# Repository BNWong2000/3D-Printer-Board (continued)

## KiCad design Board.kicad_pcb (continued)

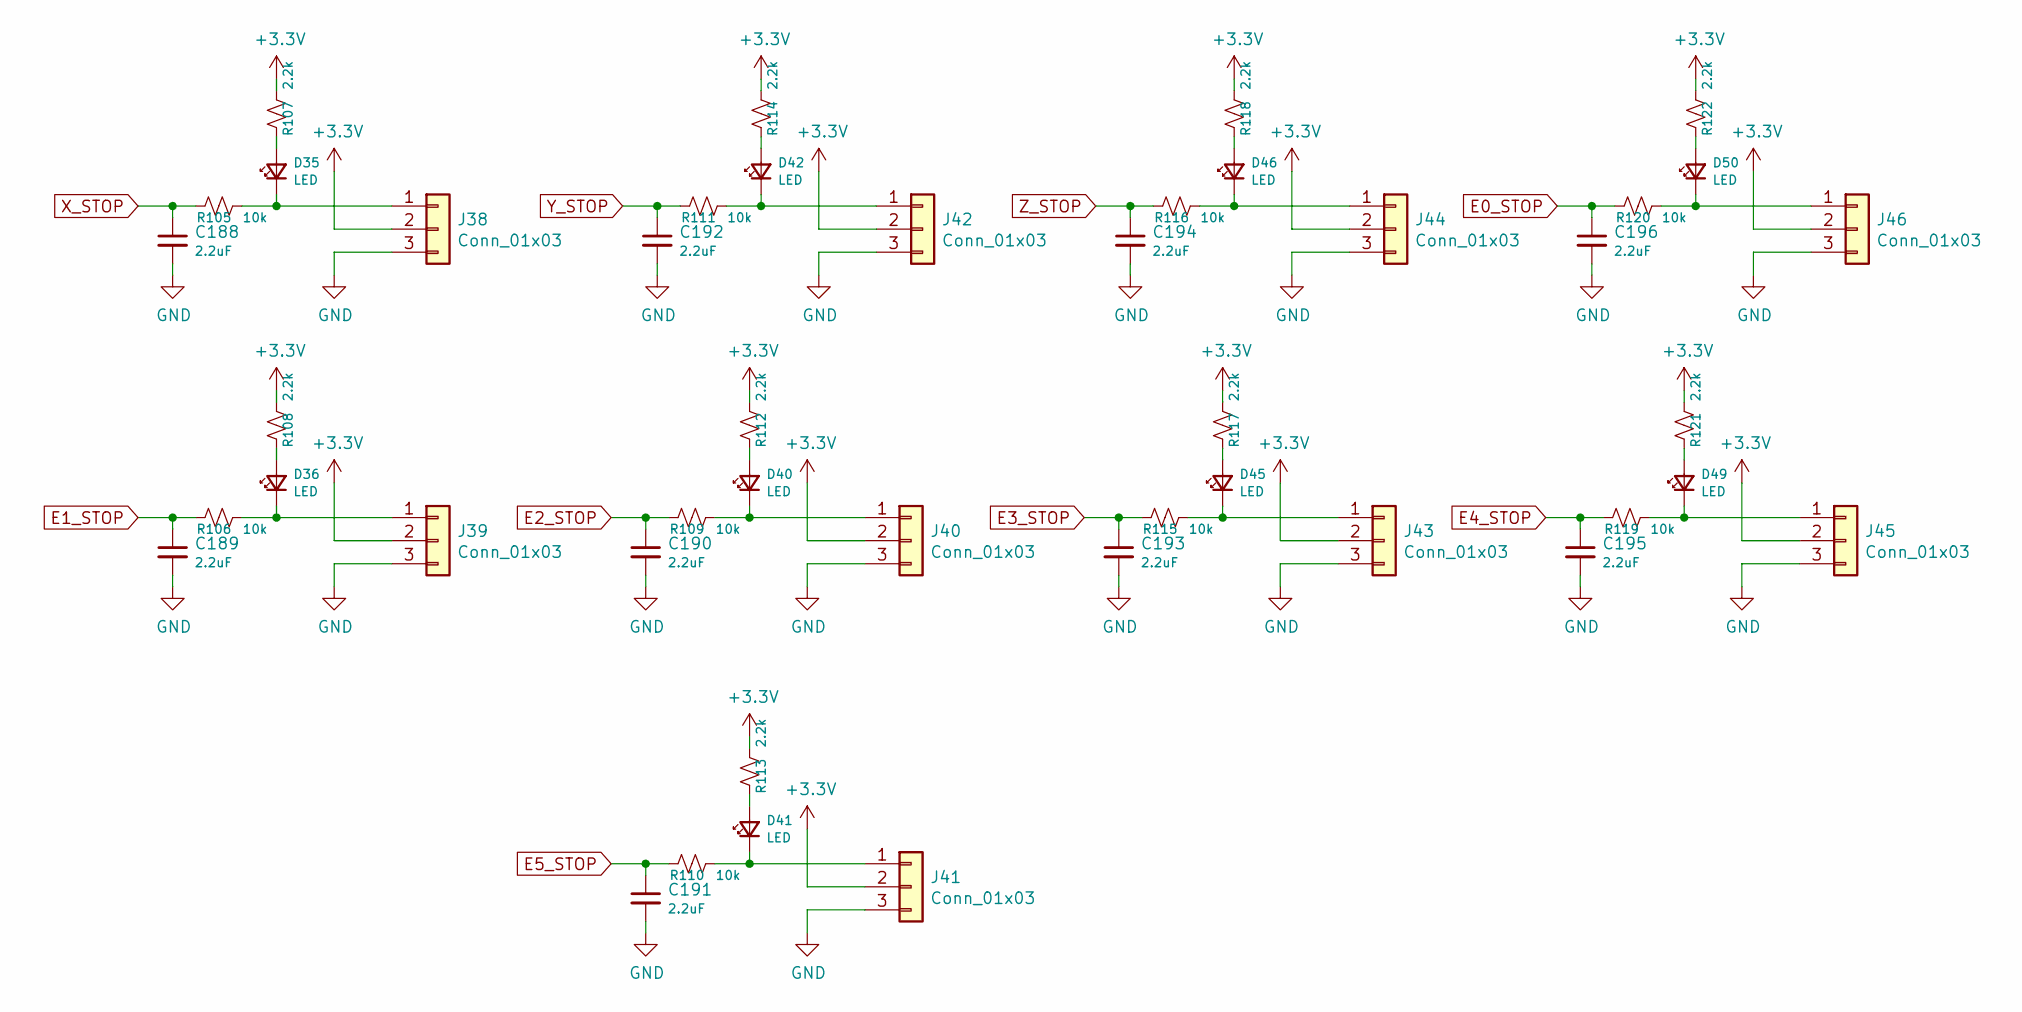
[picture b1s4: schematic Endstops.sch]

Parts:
C188, C189, C190, C191, C192, C193, C194, C195, C196: 2.2uF; C_0603_1608Metric_Pad1.05x0.95mm_HandSolder
D35, D36, D40, D41, D42, D45, D46, D49, D50: LED; LED_0603_1608Metric_Pad1.05x0.95mm_HandSolder
J38, J39, J40, J41, J42, J43, J44, J45, J46: Conn_01x03; Molex_KK-254_AE-6410-03A_1x03_P2.54mm_Vertical
R105, R106, R109, R110, R111, R115, R116, R119, R120: 10k; R_0603_1608Metric_Pad1.05x0.95mm_HandSolder
R107, R108, R112, R113, R114, R117, R118, R121, R122: 2.2k; R_0603_1608Metric_Pad1.05x0.95mm_HandSolder

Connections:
+3V3: J38.2, J39.2, J40.2, J41.2, J42.2, J43.2, J44.2, J45.2, J46.2, R107.1, R108.1, R112.1, R113.1, R114.1, R117.1, R118.1, R121.1, R122.1; also elsewhere on the board
E0_STOP: C196.1, R120.2; also elsewhere on the board
E1_STOP: C189.1, R106.2; also elsewhere on the board
E2_STOP: C190.1, R109.2; also elsewhere on the board
E3_STOP: C193.1, R115.2; also elsewhere on the board
E4_STOP: C195.1, R119.2; also elsewhere on the board
E5_STOP: C191.1, R110.2; also elsewhere on the board
GND: C188.2, C189.2, C190.2, C191.2, C192.2, C193.2, C194.2, C195.2, C196.2, J38.3, J39.3, J40.3, J41.3, J42.3, J43.3, J44.3, J45.3, J46.3; also elsewhere on the board
unnamed: D35.1 (K), J38.1, R105.1
unnamed: D35.2 (A), R107.2
unnamed: D36.1 (K), J39.1, R106.1
unnamed: D36.2 (A), R108.2
unnamed: D40.1 (K), J40.1, R109.1
unnamed: D40.2 (A), R112.2
unnamed: D41.1 (K), J41.1, R110.1
unnamed: D41.2 (A), R113.2
unnamed: D42.1 (K), J42.1, R111.1
unnamed: D42.2 (A), R114.2
unnamed: D45.1 (K), J43.1, R115.1
unnamed: D45.2 (A), R117.2
unnamed: D46.1 (K), J44.1, R116.1
unnamed: D46.2 (A), R118.2
unnamed: D49.1 (K), J45.1, R119.1
unnamed: D49.2 (A), R121.2
unnamed: D50.1 (K), J46.1, R120.1
unnamed: D50.2 (A), R122.2
X_STOP: C188.1, R105.2; also elsewhere on the board
Y_STOP: C192.1, R111.2; also elsewhere on the board
Z_STOP: C194.1, R116.2; also elsewhere on the board

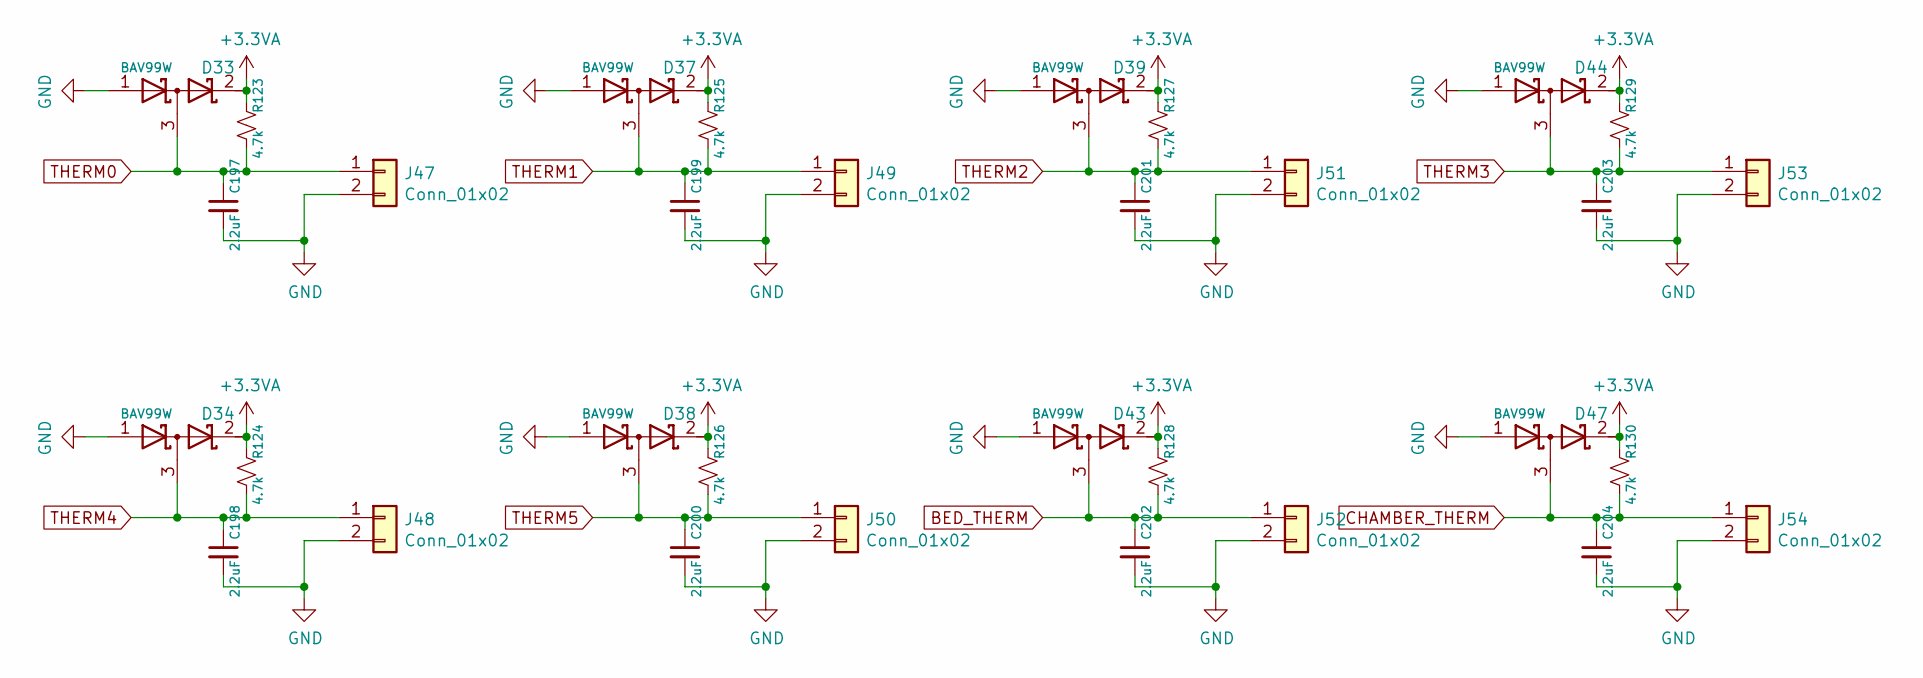
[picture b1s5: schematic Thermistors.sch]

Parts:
C197, C198, C199, C200, C201, C202, C203, C204: 2.2uF; C_0603_1608Metric_Pad1.05x0.95mm_HandSolder
D33, D34, D37, D38, D39, D43, D44, D47: BAV99W; SOT-323_SC-70_Handsoldering
J47, J48, J49, J50, J51, J52, J53, J54: Conn_01x02; Molex_KK-254_AE-6410-02A_1x02_P2.54mm_Vertical
R123, R124, R125, R126, R127, R128, R129, R130: 4.7k; R_0603_1608Metric_Pad1.05x0.95mm_HandSolder

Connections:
+3.3VA: D33.2 (K), D34.2 (K), D37.2 (K), D38.2 (K), D39.2 (K), D43.2 (K), D44.2 (K), D47.2 (K), R123.1, R124.1, R125.1, R126.1, R127.1, R128.1, R129.1, R130.1; also elsewhere on the board
BED_THERM: C202.1, D43.3 (common), J52.1, R128.2; also elsewhere on the board
CHAMBER_THERM: C204.1, D47.3 (common), J54.1, R130.2; also elsewhere on the board
GND: C197.2, C198.2, C199.2, C200.2, C201.2, C202.2, C203.2, C204.2, D33.1 (A), D34.1 (A), D37.1 (A), D38.1 (A), D39.1 (A), D43.1 (A), D44.1 (A), D47.1 (A), J47.2, J48.2, J49.2, J50.2, J51.2, J52.2, J53.2, J54.2; also elsewhere on the board
THERM0: C197.1, D33.3 (common), J47.1, R123.2; also elsewhere on the board
THERM1: C199.1, D37.3 (common), J49.1, R125.2; also elsewhere on the board
THERM2: C201.1, D39.3 (common), J51.1, R127.2; also elsewhere on the board
THERM3: C203.1, D44.3 (common), J53.1, R129.2; also elsewhere on the board
THERM4: C198.1, D34.3 (common), J48.1, R124.2; also elsewhere on the board
THERM5: C200.1, D38.3 (common), J50.1, R126.2; also elsewhere on the board

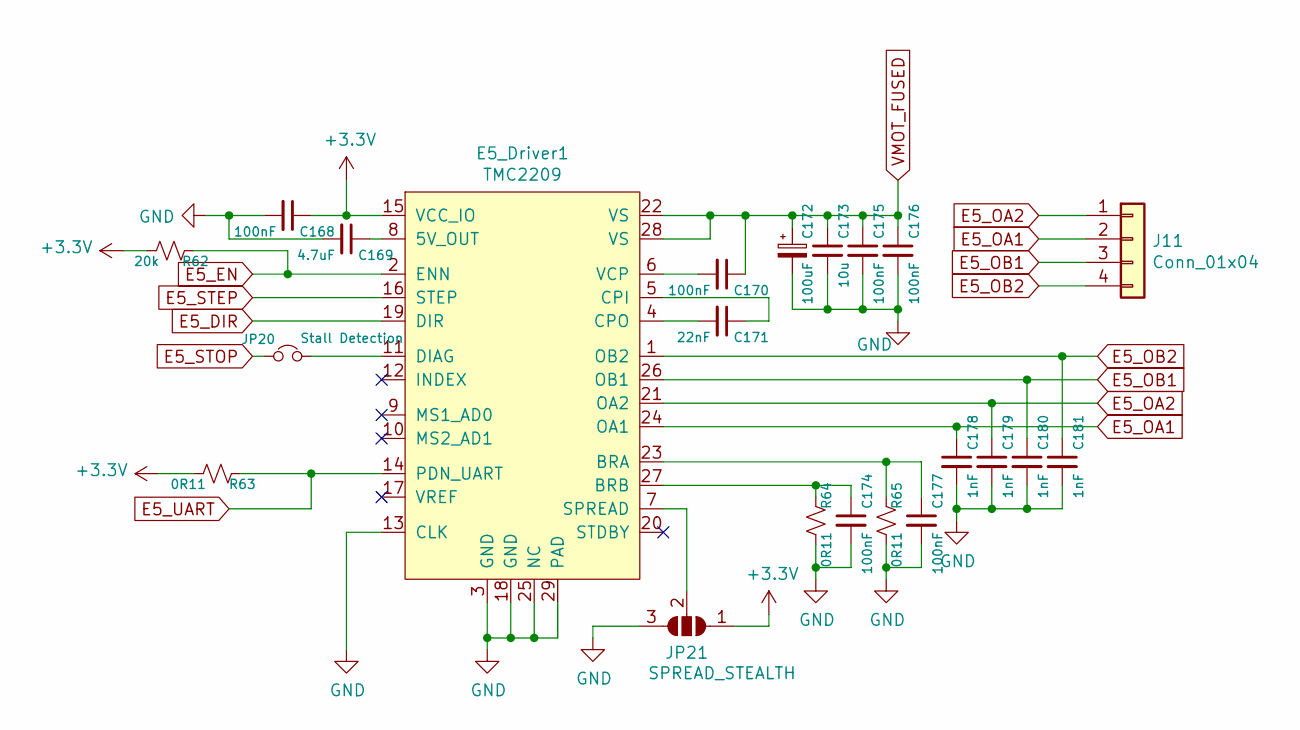
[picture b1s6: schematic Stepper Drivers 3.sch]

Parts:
C168, C170, C174, C175, C176, C177: 100nF; C_0603_1608Metric_Pad1.05x0.95mm_HandSolder
C169: 4.7uF; C_0805_2012Metric_Pad1.15x1.40mm_HandSolder
C171: 22nF; C_0603_1608Metric_Pad1.05x0.95mm_HandSolder
C172: 100uF; CP_Elec_6.3x7.7
C173: 10u; C_0805_2012Metric_Pad1.15x1.40mm_HandSolder
C178, C179, C180, C181: 1nF; C_0603_1608Metric_Pad1.05x0.95mm_HandSolder
E5_Driver1: TMC2209
J11: Conn_01x04; Molex_KK-254_AE-6410-04A_1x04_P2.54mm_Vertical
JP20: Stall Detection; PinHeader_1x02_P2.54mm_Vertical
JP21: SPREAD_STEALTH; PinHeader_1x03_P2.54mm_Vertical
R62: 20k
R63, R64, R65: 0R11

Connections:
+3V3: C168.1, E5_Driver1.15 (VCC_IO), JP21.1 (A), R62.2, R63.2; also elsewhere on the board
E5_DIR: E5_Driver1.19 (DIR); also elsewhere on the board
E5_EN: E5_Driver1.2 (ENN), R62.1; also elsewhere on the board
E5_OA1: C178.1, E5_Driver1.24 (OA1), J11.2
E5_OA2: C179.1, E5_Driver1.21 (OA2), J11.1
E5_OB1: C180.1, E5_Driver1.26 (OB1), J11.3
E5_OB2: C181.1, E5_Driver1.1 (OB2), J11.4
E5_STEP: E5_Driver1.16 (STEP); also elsewhere on the board
E5_STOP: JP20.1; also elsewhere on the board
E5_UART: E5_Driver1.14 (PDN_UART), R63.1; also elsewhere on the board
GND: C168.2, C169.2, C172.2, C173.2, C174.2, C175.2, C176.2, C177.2, C178.2, C179.2, C180.2, C181.2, E5_Driver1.3 (GND), E5_Driver1.13 (CLK), E5_Driver1.18 (GND), E5_Driver1.25 (NC), E5_Driver1.29 (PAD), JP21.3 (B), R64.2, R65.2; also elsewhere on the board
unnamed: C169.1, E5_Driver1.8 (5V_OUT)
unnamed: C170.2, E5_Driver1.6 (VCP)
unnamed: C171.1, E5_Driver1.5 (CPI)
unnamed: C171.2, E5_Driver1.4 (CPO)
unnamed: C174.1, E5_Driver1.27 (BRB), R64.1
unnamed: C177.1, E5_Driver1.23 (BRA), R65.1
unnamed: E5_Driver1.7 (SPREAD), JP21.2 (C)
unnamed: E5_Driver1.11 (DIAG), JP20.2
VMOT_FUSED: C170.1, C172.1, C173.1, C175.1, C176.1, E5_Driver1.22 (VS), E5_Driver1.28 (VS); also elsewhere on the board

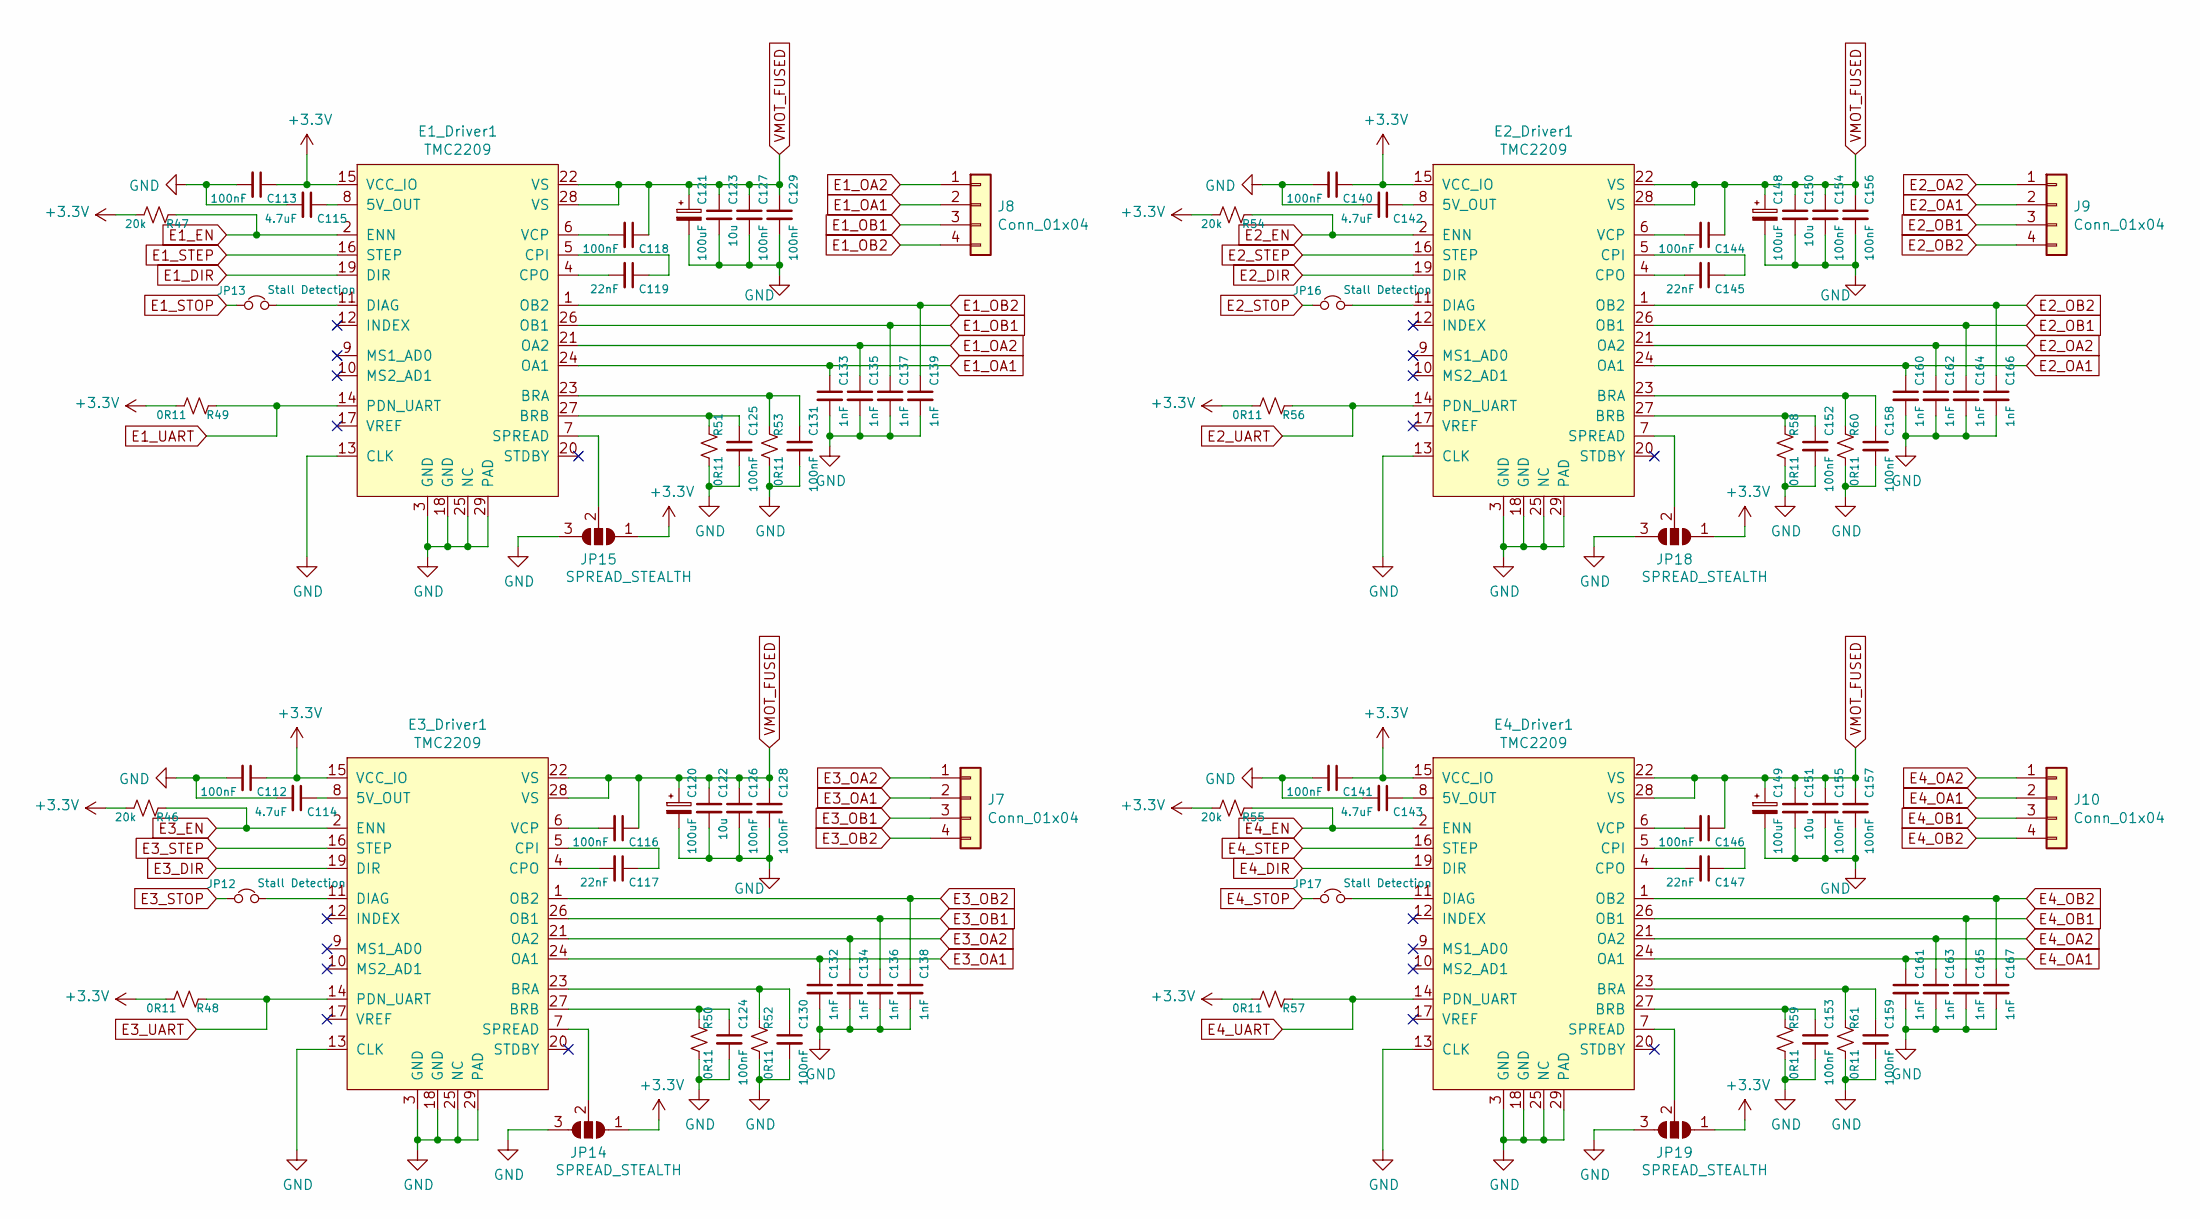
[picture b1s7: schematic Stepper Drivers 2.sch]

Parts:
C112, C113, C116, C118, C124, C125, C126, C127, C128, C129, C130, C131, C140, C141, C144, C146, C152, C153, C154, C155, C156, C157, C158, C159: 100nF; C_0603_1608Metric_Pad1.05x0.95mm_HandSolder
C114, C115, C142, C143: 4.7uF; C_0805_2012Metric_Pad1.15x1.40mm_HandSolder
C117, C119, C145, C147: 22nF; C_0603_1608Metric_Pad1.05x0.95mm_HandSolder
C120, C121, C148, C149: 100uF; CP_Elec_6.3x7.7
C122, C123, C150, C151: 10u; C_0805_2012Metric_Pad1.15x1.40mm_HandSolder
C132, C133, C134, C135, C136, C137, C138, C139, C160, C161, C162, C163, C164, C165, C166, C167: 1nF; C_0603_1608Metric_Pad1.05x0.95mm_HandSolder
E1_Driver1, E2_Driver1, E3_Driver1, E4_Driver1: TMC2209; QFN-28-1EP_5x5mm_P0.5mm_EP3.35x3.35mm_ThermalVias
J7, J8, J9, J10: Conn_01x04; Molex_KK-254_AE-6410-04A_1x04_P2.54mm_Vertical
JP12, JP13, JP16, JP17: Stall Detection; PinHeader_1x02_P2.54mm_Vertical
JP14, JP15, JP18, JP19: SPREAD_STEALTH; SolderJumper-3_P1.3mm_Open_RoundedPad1.0x1.5mm
R46, R47, R54, R55: 20k; R_0603_1608Metric_Pad1.05x0.95mm_HandSolder
R48, R49, R50, R51, R52, R53, R56, R57, R58, R59, R60, R61: 0R11; R_0805_2012Metric_Pad1.15x1.40mm_HandSolder

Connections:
+3V3: C112.1, C113.1, C140.1, C141.1, E1_Driver1.15 (VCC_IO), E2_Driver1.15 (VCC_IO), E3_Driver1.15 (VCC_IO), E4_Driver1.15 (VCC_IO), JP14.1 (A), JP15.1 (A), JP18.1 (A), JP19.1 (A), R46.2, R47.2, R48.2, R49.2, R54.2, R55.2, R56.2, R57.2; also elsewhere on the board
E1_DIR: E1_Driver1.19 (DIR); also elsewhere on the board
E1_EN: E1_Driver1.2 (ENN), R47.1; also elsewhere on the board
E1_OA1: C133.1, E1_Driver1.24 (OA1), J8.2
E1_OA2: C135.1, E1_Driver1.21 (OA2), J8.1
E1_OB1: C137.1, E1_Driver1.26 (OB1), J8.3
E1_OB2: C139.1, E1_Driver1.1 (OB2), J8.4
E1_STEP: E1_Driver1.16 (STEP); also elsewhere on the board
E1_STOP: JP13.1; also elsewhere on the board
E1_UART: E1_Driver1.14 (PDN_UART), R49.1; also elsewhere on the board
E2_DIR: E2_Driver1.19 (DIR); also elsewhere on the board
E2_EN: E2_Driver1.2 (ENN), R54.1; also elsewhere on the board
E2_OA1: C160.1, E2_Driver1.24 (OA1), J9.2
E2_OA2: C162.1, E2_Driver1.21 (OA2), J9.1
E2_OB1: C164.1, E2_Driver1.26 (OB1), J9.3
E2_OB2: C166.1, E2_Driver1.1 (OB2), J9.4
E2_STEP: E2_Driver1.16 (STEP); also elsewhere on the board
E2_STOP: JP16.1; also elsewhere on the board
E2_UART: E2_Driver1.14 (PDN_UART), R56.1; also elsewhere on the board
E3_DIR: E3_Driver1.19 (DIR); also elsewhere on the board
E3_EN: E3_Driver1.2 (ENN), R46.1; also elsewhere on the board
E3_OA1: C132.1, E3_Driver1.24 (OA1), J7.2
E3_OA2: C134.1, E3_Driver1.21 (OA2), J7.1
E3_OB1: C136.1, E3_Driver1.26 (OB1), J7.3
E3_OB2: C138.1, E3_Driver1.1 (OB2), J7.4
E3_STEP: E3_Driver1.16 (STEP); also elsewhere on the board
E3_STOP: JP12.1; also elsewhere on the board
E3_UART: E3_Driver1.14 (PDN_UART), R48.1; also elsewhere on the board
E4_DIR: E4_Driver1.19 (DIR); also elsewhere on the board
E4_EN: E4_Driver1.2 (ENN), R55.1; also elsewhere on the board
E4_OA1: C161.1, E4_Driver1.24 (OA1), J10.2
E4_OA2: C163.1, E4_Driver1.21 (OA2), J10.1
E4_OB1: C165.1, E4_Driver1.26 (OB1), J10.3
E4_OB2: C167.1, E4_Driver1.1 (OB2), J10.4
E4_STEP: E4_Driver1.16 (STEP); also elsewhere on the board
E4_STOP: JP17.1; also elsewhere on the board
E4_UART: E4_Driver1.14 (PDN_UART), R57.1; also elsewhere on the board
GND: C112.2, C113.2, C114.2, C115.2, C120.2, C121.2, C122.2, C123.2, C124.2, C125.2, C126.2, C127.2, C128.2, C129.2, C130.2, C131.2, C132.2, C133.2, C134.2, C135.2, C136.2, C137.2, C138.2, C139.2, C140.2, C141.2, C142.2, C143.2, C148.2, C149.2, C150.2, C151.2, C152.2, C153.2, C154.2, C155.2, C156.2, C157.2, C158.2, C159.2, C160.2, C161.2, C162.2, C163.2, C164.2, C165.2, C166.2, C167.2, E1_Driver1.3 (GND), E1_Driver1.13 (CLK), E1_Driver1.18 (GND), E1_Driver1.25 (NC), E1_Driver1.29 (PAD), E2_Driver1.3 (GND), E2_Driver1.13 (CLK), E2_Driver1.18 (GND), E2_Driver1.25 (NC), E2_Driver1.29 (PAD), E3_Driver1.3 (GND), E3_Driver1.13 (CLK), E3_Driver1.18 (GND), E3_Driver1.25 (NC), E3_Driver1.29 (PAD), E4_Driver1.3 (GND), E4_Driver1.13 (CLK), E4_Driver1.18 (GND), E4_Driver1.25 (NC), E4_Driver1.29 (PAD), JP14.3 (B), JP15.3 (B), JP18.3 (B), JP19.3 (B), R50.2, R51.2, R52.2, R53.2, R58.2, R59.2, R60.2, R61.2; also elsewhere on the board
unnamed: C114.1, E3_Driver1.8 (5V_OUT)
unnamed: C115.1, E1_Driver1.8 (5V_OUT)
unnamed: C116.2, E3_Driver1.6 (VCP)
unnamed: C117.1, E3_Driver1.5 (CPI)
unnamed: C117.2, E3_Driver1.4 (CPO)
unnamed: C118.2, E1_Driver1.6 (VCP)
unnamed: C119.1, E1_Driver1.5 (CPI)
unnamed: C119.2, E1_Driver1.4 (CPO)
unnamed: C124.1, E3_Driver1.27 (BRB), R50.1
unnamed: C125.1, E1_Driver1.27 (BRB), R51.1
unnamed: C130.1, E3_Driver1.23 (BRA), R52.1
unnamed: C131.1, E1_Driver1.23 (BRA), R53.1
unnamed: C142.1, E2_Driver1.8 (5V_OUT)
unnamed: C143.1, E4_Driver1.8 (5V_OUT)
unnamed: C144.2, E2_Driver1.6 (VCP)
unnamed: C145.1, E2_Driver1.5 (CPI)
unnamed: C145.2, E2_Driver1.4 (CPO)
unnamed: C146.2, E4_Driver1.6 (VCP)
unnamed: C147.1, E4_Driver1.5 (CPI)
unnamed: C147.2, E4_Driver1.4 (CPO)
unnamed: C152.1, E2_Driver1.27 (BRB), R58.1
unnamed: C153.1, E4_Driver1.27 (BRB), R59.1
unnamed: C158.1, E2_Driver1.23 (BRA), R60.1
unnamed: C159.1, E4_Driver1.23 (BRA), R61.1
unnamed: E1_Driver1.7 (SPREAD), JP15.2 (C)
unnamed: E1_Driver1.11 (DIAG), JP13.2
unnamed: E2_Driver1.7 (SPREAD), JP18.2 (C)
unnamed: E2_Driver1.11 (DIAG), JP16.2
unnamed: E3_Driver1.7 (SPREAD), JP14.2 (C)
unnamed: E3_Driver1.11 (DIAG), JP12.2
unnamed: E4_Driver1.7 (SPREAD), JP19.2 (C)
unnamed: E4_Driver1.11 (DIAG), JP17.2
VMOT_FUSED: C116.1, C118.1, C120.1, C121.1, C122.1, C123.1, C126.1, C127.1, C128.1, C129.1, C144.1, C146.1, C148.1, C149.1, C150.1, C151.1, C154.1, C155.1, C156.1, C157.1, E1_Driver1.22 (VS), E1_Driver1.28 (VS), E2_Driver1.22 (VS), E2_Driver1.28 (VS), E3_Driver1.22 (VS), E3_Driver1.28 (VS), E4_Driver1.22 (VS), E4_Driver1.28 (VS); also elsewhere on the board

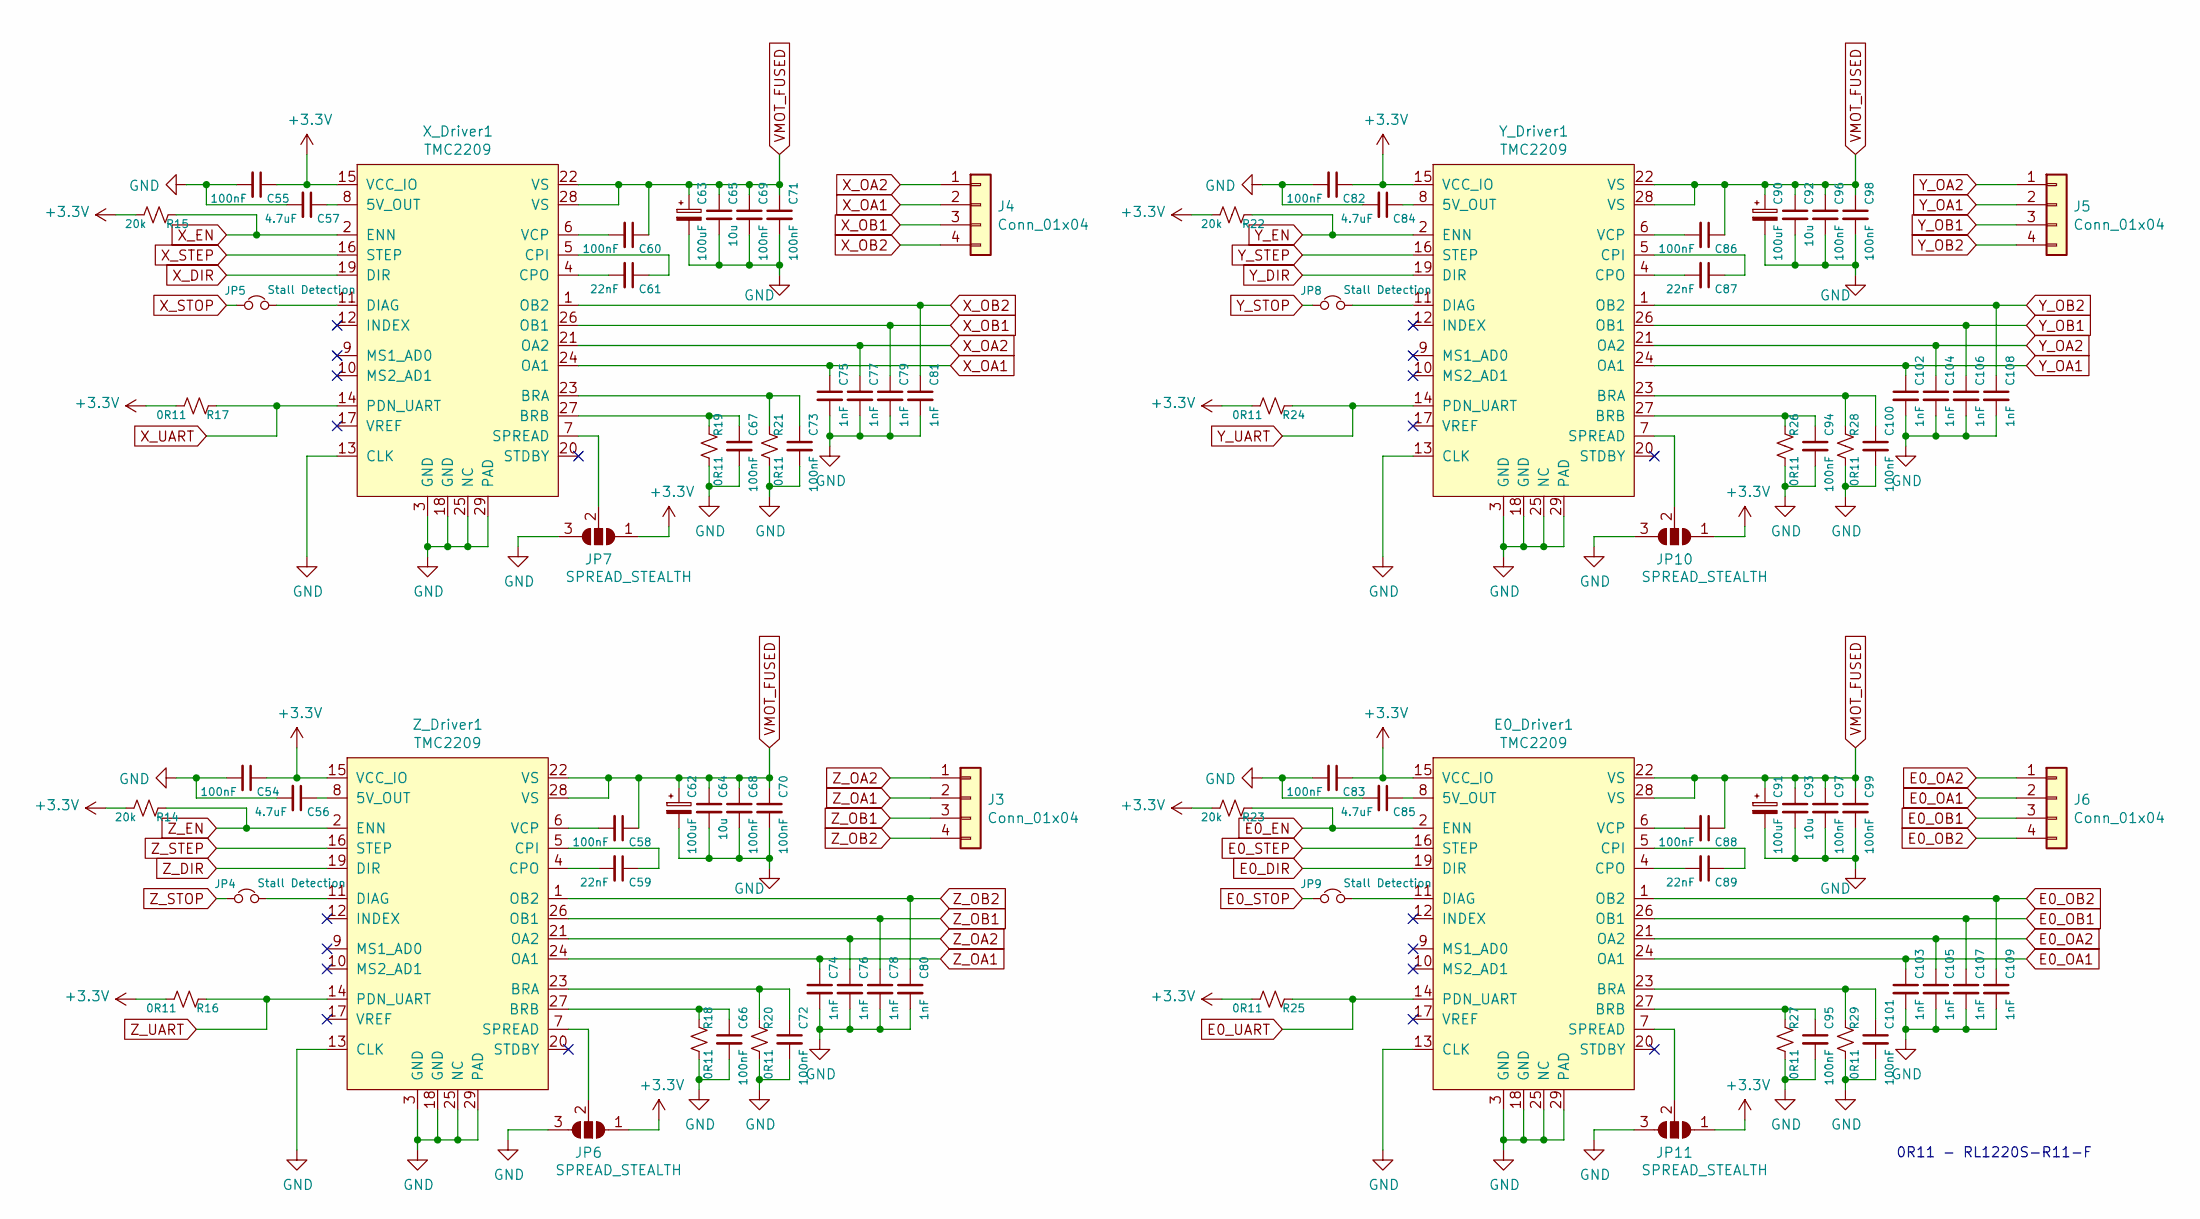
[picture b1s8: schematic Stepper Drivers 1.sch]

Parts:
C54, C55, C58, C60, C66, C67, C68, C69, C70, C71, C72, C73, C82, C83, C86, C88, C94, C95, C96, C97, C98, C99, C100, C101: 100nF; C_0603_1608Metric_Pad1.05x0.95mm_HandSolder
C56, C57, C84, C85: 4.7uF; C_0805_2012Metric_Pad1.15x1.40mm_HandSolder
C59, C61, C87, C89: 22nF; C_0603_1608Metric_Pad1.05x0.95mm_HandSolder
C62, C63, C90, C91: 100uF; CP_Elec_6.3x7.7
C64, C65, C92, C93: 10u; C_0805_2012Metric_Pad1.15x1.40mm_HandSolder
C74, C75, C76, C77, C78, C79, C80, C81, C102, C103, C104, C105, C106, C107, C108, C109: 1nF; C_0603_1608Metric_Pad1.05x0.95mm_HandSolder
E0_Driver1: TMC2209; QFN-28-1EP_5x5mm_P0.5mm_EP3.35x3.35mm_ThermalVias
J3, J4, J5, J6: Conn_01x04; Molex_KK-254_AE-6410-04A_1x04_P2.54mm_Vertical
JP4, JP5, JP8, JP9: Stall Detection; PinHeader_1x02_P2.54mm_Vertical
JP6, JP7, JP10, JP11: SPREAD_STEALTH; SolderJumper-3_P1.3mm_Open_RoundedPad1.0x1.5mm
R14, R15, R22, R23: 20k; R_0603_1608Metric_Pad1.05x0.95mm_HandSolder
R16, R17, R18, R19, R20, R21, R24, R25, R26, R27, R28, R29: 0R11; R_0805_2012Metric_Pad1.15x1.40mm_HandSolder
X_Driver1: TMC2209; QFN-28-1EP_5x5mm_P0.5mm_EP3.35x3.35mm_ThermalVias
Y_Driver1: TMC2209; QFN-28-1EP_5x5mm_P0.5mm_EP3.35x3.35mm_ThermalVias
Z_Driver1: TMC2209; QFN-28-1EP_5x5mm_P0.5mm_EP3.35x3.35mm_ThermalVias

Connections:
+3V3: C54.1, C55.1, C82.1, C83.1, E0_Driver1.15 (VCC_IO), JP6.1 (A), JP7.1 (A), JP10.1 (A), JP11.1 (A), R14.2, R15.2, R16.2, R17.2, R22.2, R23.2, R24.2, R25.2, X_Driver1.15 (VCC_IO), Y_Driver1.15 (VCC_IO), Z_Driver1.15 (VCC_IO); also elsewhere on the board
E0_DIR: E0_Driver1.19 (DIR); also elsewhere on the board
E0_EN: E0_Driver1.2 (ENN), R23.1; also elsewhere on the board
E0_OA1: C103.1, E0_Driver1.24 (OA1), J6.2
E0_OA2: C105.1, E0_Driver1.21 (OA2), J6.1
E0_OB1: C107.1, E0_Driver1.26 (OB1), J6.3
E0_OB2: C109.1, E0_Driver1.1 (OB2), J6.4
E0_STEP: E0_Driver1.16 (STEP); also elsewhere on the board
E0_STOP: JP9.1; also elsewhere on the board
E0_UART: E0_Driver1.14 (PDN_UART), R25.1; also elsewhere on the board
GND: C54.2, C55.2, C56.2, C57.2, C62.2, C63.2, C64.2, C65.2, C66.2, C67.2, C68.2, C69.2, C70.2, C71.2, C72.2, C73.2, C74.2, C75.2, C76.2, C77.2, C78.2, C79.2, C80.2, C81.2, C82.2, C83.2, C84.2, C85.2, C90.2, C91.2, C92.2, C93.2, C94.2, C95.2, C96.2, C97.2, C98.2, C99.2, C100.2, C101.2, C102.2, C103.2, C104.2, C105.2, C106.2, C107.2, C108.2, C109.2, E0_Driver1.3 (GND), E0_Driver1.13 (CLK), E0_Driver1.18 (GND), E0_Driver1.25 (NC), E0_Driver1.29 (PAD), JP6.3 (B), JP7.3 (B), JP10.3 (B), JP11.3 (B), R18.2, R19.2, R20.2, R21.2, R26.2, R27.2, R28.2, R29.2, X_Driver1.3 (GND), X_Driver1.13 (CLK), X_Driver1.18 (GND), X_Driver1.25 (NC), X_Driver1.29 (PAD), Y_Driver1.3 (GND), Y_Driver1.13 (CLK), Y_Driver1.18 (GND), Y_Driver1.25 (NC), Y_Driver1.29 (PAD), Z_Driver1.3 (GND), Z_Driver1.13 (CLK), Z_Driver1.18 (GND), Z_Driver1.25 (NC), Z_Driver1.29 (PAD); also elsewhere on the board
unnamed: C56.1, Z_Driver1.8 (5V_OUT)
unnamed: C57.1, X_Driver1.8 (5V_OUT)
unnamed: C58.2, Z_Driver1.6 (VCP)
unnamed: C59.1, Z_Driver1.5 (CPI)
unnamed: C59.2, Z_Driver1.4 (CPO)
unnamed: C60.2, X_Driver1.6 (VCP)
unnamed: C61.1, X_Driver1.5 (CPI)
unnamed: C61.2, X_Driver1.4 (CPO)
unnamed: C66.1, R18.1, Z_Driver1.27 (BRB)
unnamed: C67.1, R19.1, X_Driver1.27 (BRB)
unnamed: C72.1, R20.1, Z_Driver1.23 (BRA)
unnamed: C73.1, R21.1, X_Driver1.23 (BRA)
unnamed: C84.1, Y_Driver1.8 (5V_OUT)
unnamed: C85.1, E0_Driver1.8 (5V_OUT)
unnamed: C86.2, Y_Driver1.6 (VCP)
unnamed: C87.1, Y_Driver1.5 (CPI)
unnamed: C87.2, Y_Driver1.4 (CPO)
unnamed: C88.2, E0_Driver1.6 (VCP)
unnamed: C89.1, E0_Driver1.5 (CPI)
unnamed: C89.2, E0_Driver1.4 (CPO)
unnamed: C94.1, R26.1, Y_Driver1.27 (BRB)
unnamed: C95.1, E0_Driver1.27 (BRB), R27.1
unnamed: C100.1, R28.1, Y_Driver1.23 (BRA)
unnamed: C101.1, E0_Driver1.23 (BRA), R29.1
unnamed: E0_Driver1.7 (SPREAD), JP11.2 (C)
unnamed: E0_Driver1.11 (DIAG), JP9.2
unnamed: JP4.2, Z_Driver1.11 (DIAG)
unnamed: JP5.2, X_Driver1.11 (DIAG)
unnamed: JP6.2 (C), Z_Driver1.7 (SPREAD)
unnamed: JP7.2 (C), X_Driver1.7 (SPREAD)
unnamed: JP8.2, Y_Driver1.11 (DIAG)
unnamed: JP10.2 (C), Y_Driver1.7 (SPREAD)
VMOT_FUSED: C58.1, C60.1, C62.1, C63.1, C64.1, C65.1, C68.1, C69.1, C70.1, C71.1, C86.1, C88.1, C90.1, C91.1, C92.1, C93.1, C96.1, C97.1, C98.1, C99.1, E0_Driver1.22 (VS), E0_Driver1.28 (VS), X_Driver1.22 (VS), X_Driver1.28 (VS), Y_Driver1.22 (VS), Y_Driver1.28 (VS), Z_Driver1.22 (VS), Z_Driver1.28 (VS); also elsewhere on the board
X_DIR: X_Driver1.19 (DIR); also elsewhere on the board
X_EN: R15.1, X_Driver1.2 (ENN); also elsewhere on the board
X_OA1: C75.1, J4.2, X_Driver1.24 (OA1)
X_OA2: C77.1, J4.1, X_Driver1.21 (OA2)
X_OB1: C79.1, J4.3, X_Driver1.26 (OB1)
X_OB2: C81.1, J4.4, X_Driver1.1 (OB2)
X_STEP: X_Driver1.16 (STEP); also elsewhere on the board
X_STOP: JP5.1; also elsewhere on the board
X_UART: R17.1, X_Driver1.14 (PDN_UART); also elsewhere on the board
Y_DIR: Y_Driver1.19 (DIR); also elsewhere on the board
Y_EN: R22.1, Y_Driver1.2 (ENN); also elsewhere on the board
Y_OA1: C102.1, J5.2, Y_Driver1.24 (OA1)
Y_OA2: C104.1, J5.1, Y_Driver1.21 (OA2)
Y_OB1: C106.1, J5.3, Y_Driver1.26 (OB1)
Y_OB2: C108.1, J5.4, Y_Driver1.1 (OB2)
Y_STEP: Y_Driver1.16 (STEP); also elsewhere on the board
Y_STOP: JP8.1; also elsewhere on the board
Y_UART: R24.1, Y_Driver1.14 (PDN_UART); also elsewhere on the board
Z_DIR: Z_Driver1.19 (DIR); also elsewhere on the board
Z_EN: R14.1, Z_Driver1.2 (ENN); also elsewhere on the board
Z_OA1: C74.1, J3.2, Z_Driver1.24 (OA1)
Z_OA2: C76.1, J3.1, Z_Driver1.21 (OA2)
Z_OB1: C78.1, J3.3, Z_Driver1.26 (OB1)
Z_OB2: C80.1, J3.4, Z_Driver1.1 (OB2)
Z_STEP: Z_Driver1.16 (STEP); also elsewhere on the board
Z_STOP: JP4.1; also elsewhere on the board
Z_UART: R16.1, Z_Driver1.14 (PDN_UART); also elsewhere on the board

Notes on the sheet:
0R11 - RL1220S-R11-F

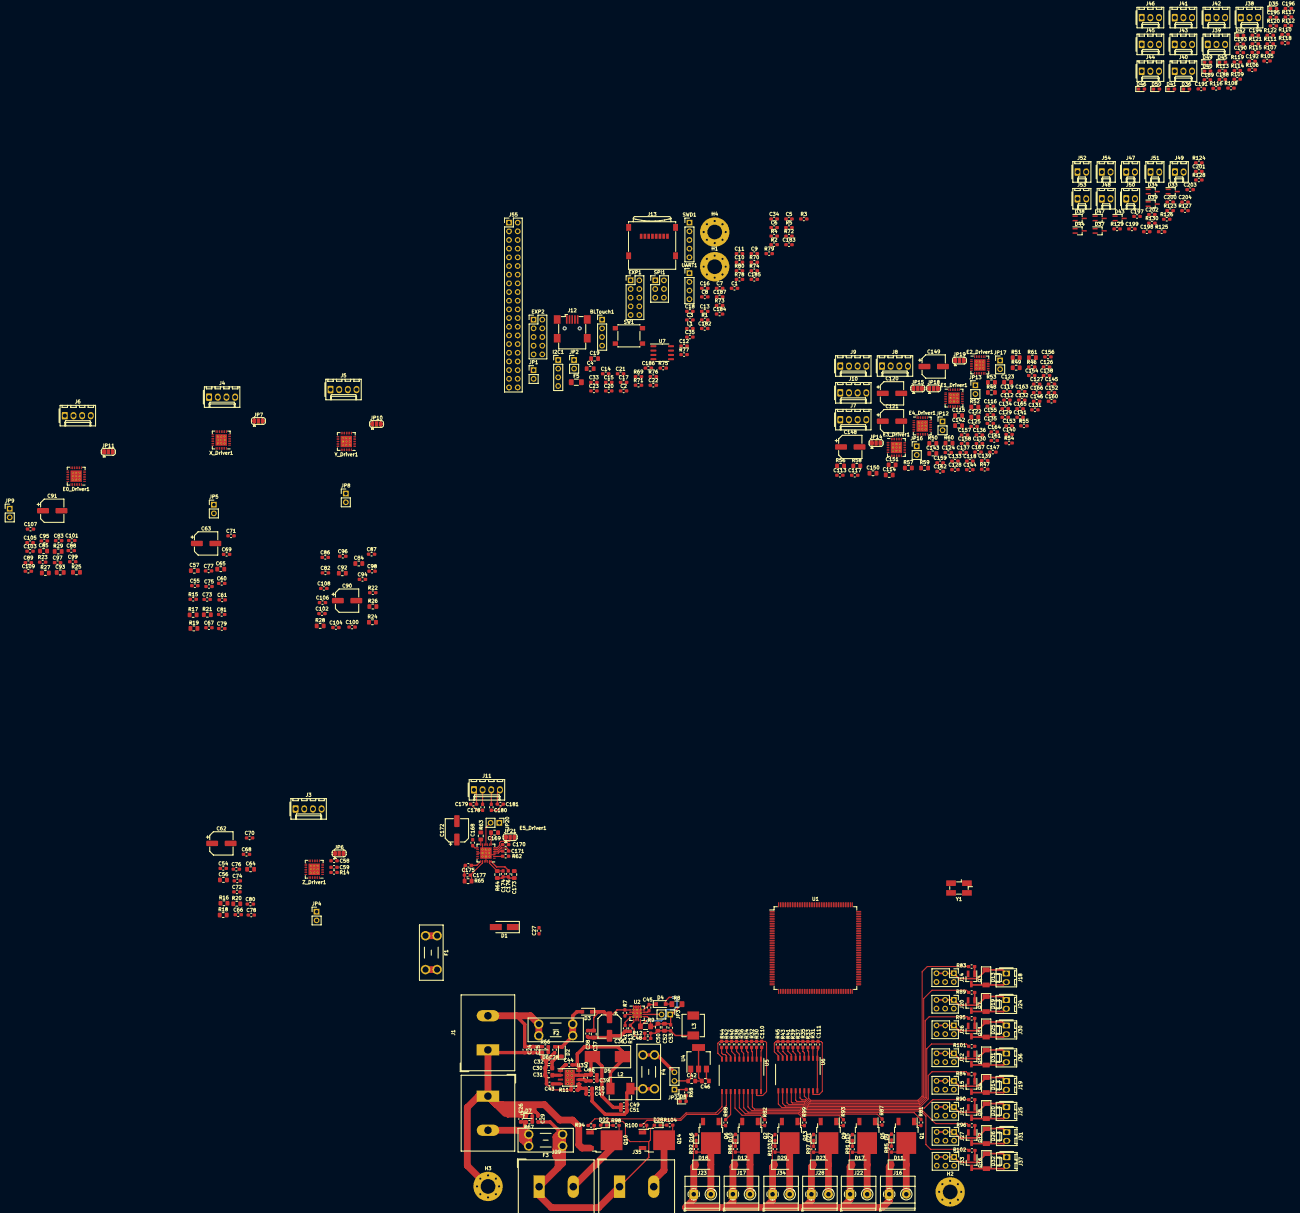
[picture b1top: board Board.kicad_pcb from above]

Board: 4 copper layers, 511 parts (0 on the bottom side), 342 nets.

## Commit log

2020-10-26 Initial Commit.
2020-10-29 added library for MOSFET Drivers
2020-10-29 small change - Resized one of the symbols to make it look nicer
2020-10-29 Started implementing MOSFET drivers
2020-10-29 added resistor numbers
2020-10-29 added MOSFETs schematic for fans and heaters.
2020-10-29 added endstop schematic
2020-10-29 Added thermistor schem
2020-10-29 small revisions
2020-10-30 added USB and micro SD card
2020-10-30 added EEPROM and peripheral libraries
2020-10-30 Completed Labelling of Schematic - All nets attached
2020-10-30 added raspberry pi header
2020-10-30 generated BOM
2020-10-30 added library
2020-11-01 assigned some footprints
2020-11-02 associated more footprints
2020-11-02 Added more footprints
2020-11-02 finished associating footprints with symbols
2020-11-02 started initial layout
2020-11-02 Roughtly Layed out power converters and FETs
2020-11-10 started some routing
2020-11-10 small component placement
2020-11-11 routed mosfets and buffers
